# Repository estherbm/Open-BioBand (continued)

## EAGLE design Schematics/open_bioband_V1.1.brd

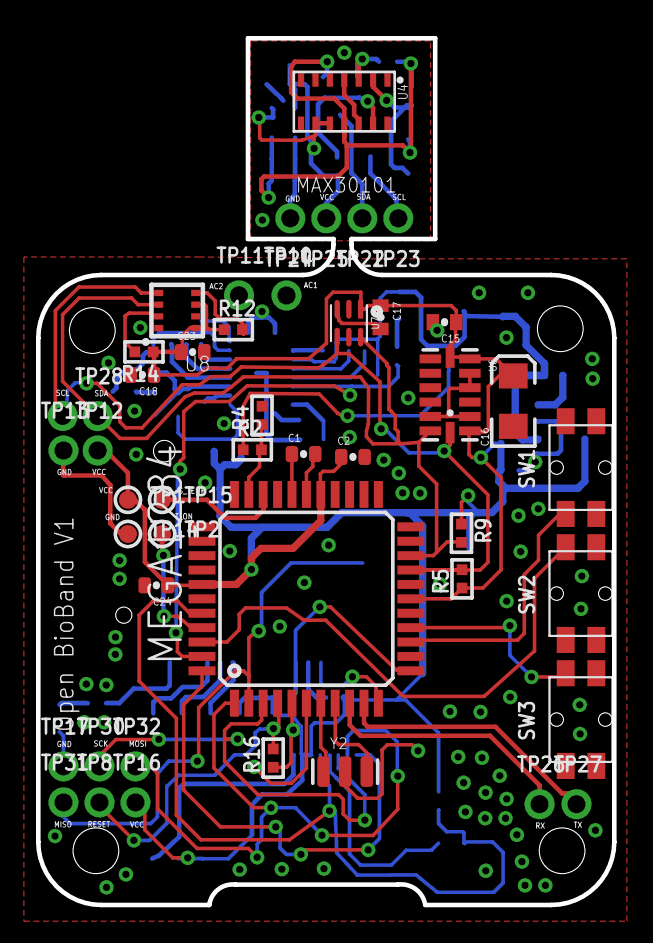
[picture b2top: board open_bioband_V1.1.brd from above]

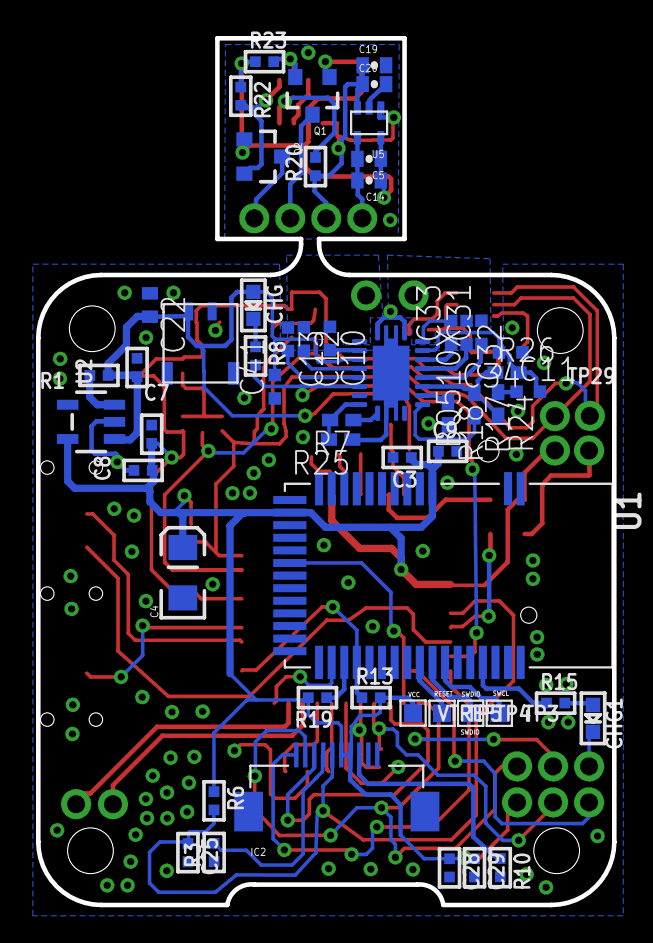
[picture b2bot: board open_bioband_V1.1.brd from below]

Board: 2 copper layers, 32.0 x 48.1 mm, 100 parts (55 on the bottom side), 58 nets.

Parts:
BQ510X: BQ24120; R-PQFP-N20
C1, C2, C5, C15, C17, C18, C20, C23, C24: 0.1uF; 0402-CAP
C3, C7, C9: 1uF; _0402
C4, C16: 10uF; EIA3216
C6, C8: 10µF; _0402
C10, C33: 0.01uF; C0402_LIBELIUM
C11, C41: 4.7uF; C0402_LIBELIUM
C12, C32: 0.47uF; C0402_LIBELIUM
C13, C31, C34: 0.022uF; C0402_LIBELIUM
C14: 4.7uF; 0402-CAP
C19: 10uF; 0402-CAP
C22: 4.7uF; C0402
C25: 0.1µF; _0402
C28, C29: 1µF; _0402
CHG: ORANGE; CHIPLED_0603
CHG1: BLUE; CHIPLED_0603
IC2: LS013B4DN04; FPC_10PIN_52892-1095
MEGA1284: TQFP44
Q1, Q2: 200mA/50V; SOT23-3
R1, R2: 100k; _0402
R3, R6, R10: 10k; _0402
R4, R13, R19: 100K; _0402
R5, R9, R12, R14, R16, R20, R22, R23: 4.7K; _0402
R7: 2.43K; R0402_LIBELIUM
R8: 1K; _0402
R15: 1k; _0402
R17: 3.83K; R0402_LIBELIUM
R18: 10k; R0402_LIBELIUM
R24: 140; R0402_LIBELIUM
R25: 0; R0402_LIBELIUM
R26: 100k; R0402_LIBELIUM
SW1, SW2, SW3: TACT_SMD2
TP1, TP2, TP14, TP15: TESTPOINT_ROUND_1MM
TP3: SWCLK; TESTPOINT_PAD_1MM
TP4: SWDIO; TESTPOINT_PAD_1MM
TP5: FCTRST; TESTPOINT_PAD_1MM
TP8, TP10, TP11, TP12, TP13, TP16, TP17, TP22, TP23, TP24, TP25, TP26, TP27, TP28, TP29, TP30, TP31, TP32: 1X01_ROUND
U1: BLE_MODULE_RAYTAC_MDBT40
U2: AP2112-3.3; SOT23-5
U4: MAX30101; OLGA-14
U5: 1.8V/100mA; SC70
U6: ADXL345ORIG; LGA14
U7: TSL2561FN; FN-6
U8: BME280; BME280_LGA
U$3: DF57H; DF57H-2P
VTREF: FCTRST; TESTPOINT_PAD_1MM
Y2: RESONATORSMD; RESONATOR-SMD

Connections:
1.8V: C5.1, C14.1, Q1.1, Q2.1, R22.1, R23.1, U4.11, U5.5
5: MEGA1284.41, TP2.P$1
!CS: R14.2, U8.P$2
!INT: R20.2, U4.13
!RESET: MEGA1284.4, R16.2, TP8.1
+3V3: C2.1, C3.1, C4.A, C7.1, C8.1, C9.1, C15.1, C16.A, C17.1, C18.1, C23.1, C24.1, C28.1, C29.1, IC2.P$6, IC2.P$7, MEGA1284.5, MEGA1284.17, MEGA1284.27, MEGA1284.38, R5.1, R6.1, R9.1, R12.1, R13.2, R14.1, R16.1, R19.2, TP1.P$1, TP12.1, TP16.1, U1.3, U1.14, U2.5, U6.1, U6.6, U6.7, U7.1, U8.P$6, U8.P$8, VTREF.P$1
+3V31: C19.1, C20.1, R20.1, TP25.1, U4.9, U4.10, U5.1, U5.3
A2: MEGA1284.32, R2.2, R4.1
AC1: BQ510X.2, C10.1, C12.1, C13.1, TP10.1
AC2: BQ510X.19, C31.2, C32.1, C33.2, TP11.1
AREF: C1.1, MEGA1284.29
BOOT3: BQ510X.3, C10.2
CHG: BQ510X.7, MEGA1284.43, R8.2
CLMP2: BQ510X.16, C32.2
CONNECTED_LED: R15.1, U1.39
DISP: C25.1, IC2.P$5, MEGA1284.40, R6.2
EN: R1.2, U2.3
EXTCOMIN: IC2.P$4, R3.2
EXTMODE: IC2.P$8, R10.1
FCTRYRST_3V: TP5.P$1, U1.34
FOD: BQ510X.14, R17.1, R24.2, R26.1
GND: BQ510X.1, BQ510X.9, BQ510X.20, C1.2, C2.2, C3.2, C4.C, C6.2, C7.2, C8.2, C9.2, C11.1, C15.2, C16.C, C17.2, C18.2, C22.1, C23.2, C24.2, C25.2, C28.2, C29.2, C34.1, C41.1, CHG1.C, IC2.P$9, IC2.P$10, MEGA1284.6, MEGA1284.18, MEGA1284.28, MEGA1284.39, R3.1, R4.2, R7.2, R10.2, R18.2, R19.1, R24.1, R25.2, SW1.2, SW1.4, SW2.2, SW2.4, SW3.2, SW3.4, TP13.1, TP14.P$1, TP17.1, U1.1, U1.2, U1.13, U1.16, U1.25, U1.28, U1.42, U2.2, U6.2, U6.4, U6.5, U6.12, U7.3, U8.P$1, U8.P$7, U$3.P$2, U$3.P$3, U$3.P$4, Y2.2
GND1: C5.2, C14.2, C19.2, C20.2, TP24.1, U4.4, U4.12, U5.2, U5.4
LV_SCL: Q2.2, R22.2, U4.2
LV_SDA: Q1.2, R23.2, U4.3
MISO: MEGA1284.2, TP31.1, U1.18
MOSI: IC2.P$2, MEGA1284.1, TP32.1
unnamed: CHG.C, R8.1
unnamed: MEGA1284.7, Y2.1
unnamed: CHG1.A, R15.2
unnamed: MEGA1284.8, Y2.3
unnamed: BQ510X.6, C13.2
unnamed: BQ510X.5, C12.2
unnamed: BQ510X.10, R7.1
unnamed: BQ510X.17, C33.1
unnamed: BQ510X.18, C11.2, C34.2, R26.2
unnamed: BQ510X.15, C31.1
unnamed: BQ510X.12, R17.2
unnamed: BQ510X.E@1, BQ510X.E@2, BQ510X.E@3, BQ510X.E@4, R25.1
NAV_DOWN: MEGA1284.15, SW3.3
NAV_SEL: MEGA1284.42, SW2.3
NAV_UP: MEGA1284.14, SW1.1
OUT: BQ510X.4, C6.1, C22.2, C41.2, CHG.A, R1.1, R2.1, U2.1, U$3.P$1
P0.5: BQ510X.13, R18.1
RX: MEGA1284.9, TP26.1
RX1: MEGA1284.11, U1.27
SCL: MEGA1284.19, R5.2, TP29.1, U6.14, U7.4, U8.P$4
SCL1: Q2.3, TP23.1
SCLK: IC2.P$1, MEGA1284.44
SCS: IC2.P$3, MEGA1284.3, TP30.1
SDA: MEGA1284.20, R9.2, TP28.1, U6.13, U7.6, U8.P$3
SDA1: Q1.3, TP22.1
SDO/ADR: R12.2, U8.P$5
SWCLK: TP3.P$1, U1.36
SWDIO/RST_3V: TP4.P$1, U1.35
S_TEMP: MEGA1284.31, TP15.P$1
TX: MEGA1284.10, TP27.1
TX1: MEGA1284.12, R13.1, U1.29
